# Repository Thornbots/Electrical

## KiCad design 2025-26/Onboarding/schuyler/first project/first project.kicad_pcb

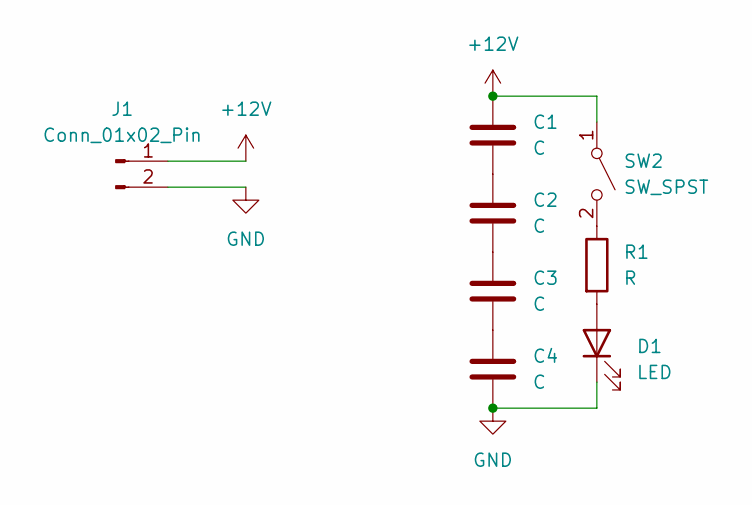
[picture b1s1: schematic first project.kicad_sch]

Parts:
C1, C2, C3, C4: C; CP_Radial_D18.0mm_P7.50mm
D1: LED; LED_D10.0mm
J1: Conn_01x02_Pin; AMASS_XT30PW-F_1x02_P2.50mm_Horizontal
R1: R; R_Axial_DIN0204_L3.6mm_D1.6mm_P5.08mm_Vertical
SW2: SW_SPST; SW_SPST_CK_RS282G05A3

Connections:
+12V: C1.1, J1.1, SW2.1 (A)
GND: C4.2, D1.1 (K), J1.2
unnamed: C1.2, C2.1
unnamed: C2.2, C3.1
unnamed: C3.2, C4.1
unnamed: D1.2 (A), R1.2
unnamed: R1.1, SW2.2 (B)

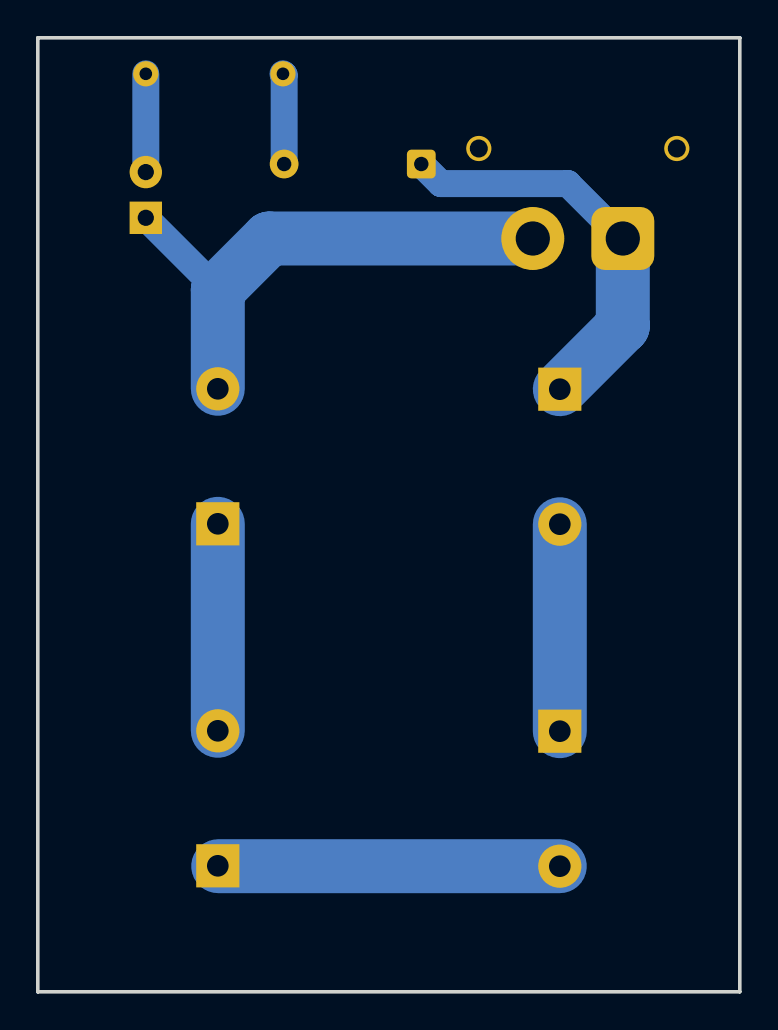
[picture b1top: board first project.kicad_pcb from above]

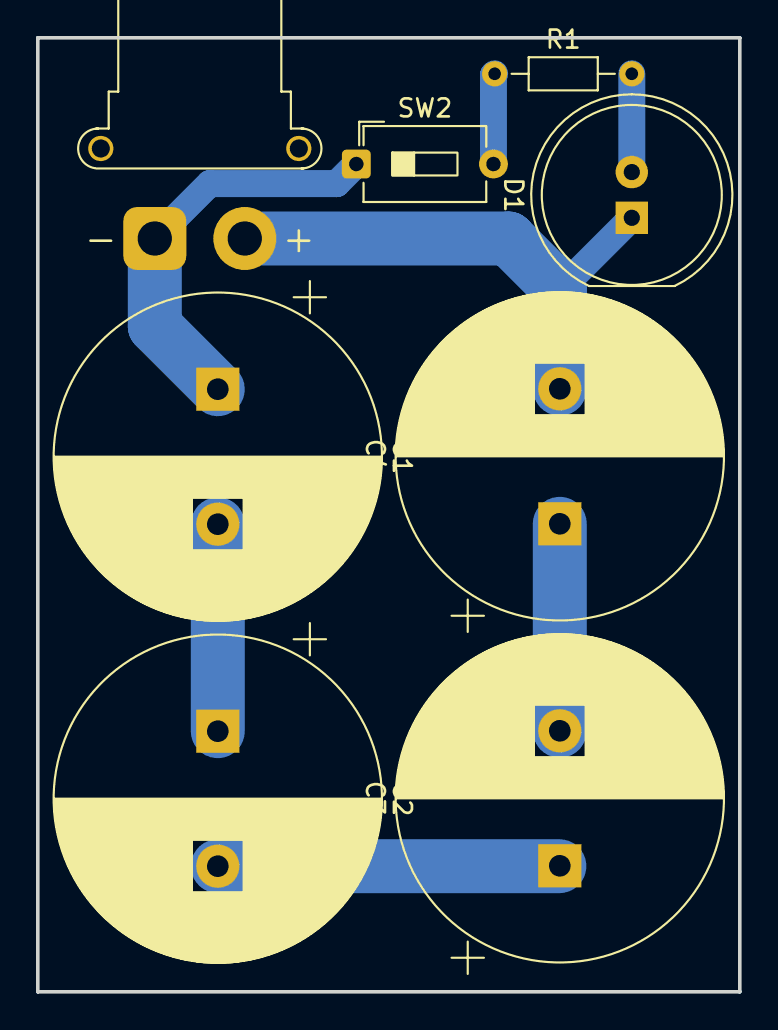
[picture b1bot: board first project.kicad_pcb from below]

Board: 2 copper layers, 39.0 x 53.0 mm, 8 parts (8 on the bottom side), 7 nets.

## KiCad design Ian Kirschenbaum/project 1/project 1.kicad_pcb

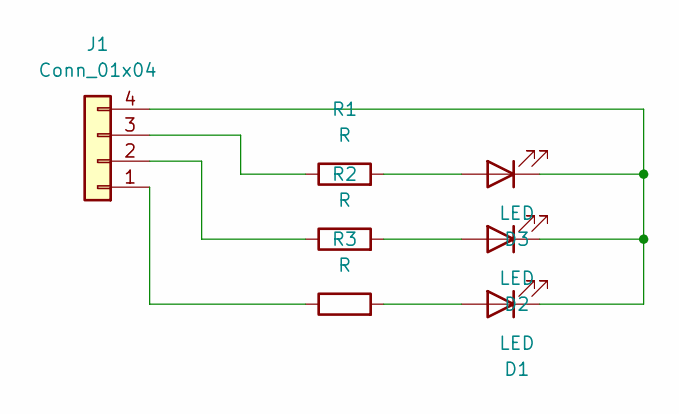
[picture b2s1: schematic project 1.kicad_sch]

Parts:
D1, D2, D3: LED
J1: Conn_01x04
R1, R2, R3: R

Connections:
unnamed: D1.2 (A), R3.2
unnamed: D1.1 (K), D2.1 (K), D3.1 (K), J1.4
unnamed: D2.2 (A), R2.2
unnamed: D3.2 (A), R1.2
unnamed: J1.1, R3.1
unnamed: J1.2, R2.1
unnamed: J1.3, R1.1

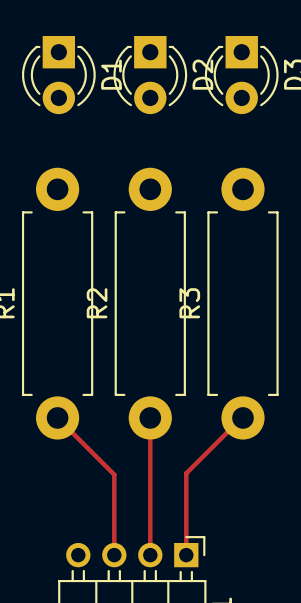
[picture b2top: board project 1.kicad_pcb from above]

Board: 2 copper layers, 7 parts (0 on the bottom side), 7 nets.

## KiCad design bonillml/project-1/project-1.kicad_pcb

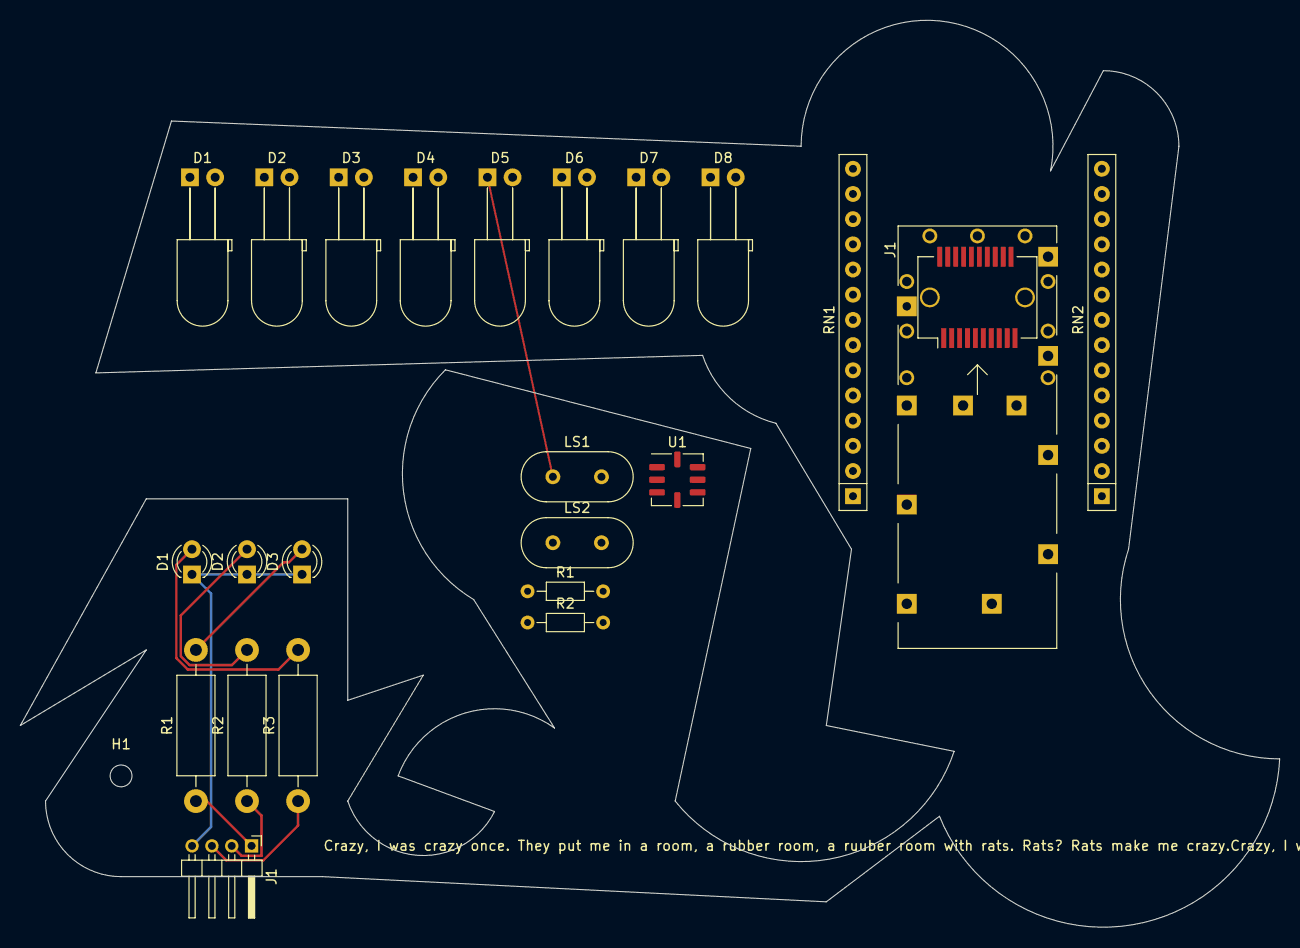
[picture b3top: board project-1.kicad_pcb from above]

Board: 2 copper layers, 127.0 x 91.5 mm, 24 parts (0 on the bottom side), 23 nets.

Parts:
D1, D2, D3, D4, D5, D6, D7, D8: LED; LED_D5.0mm_Horizontal_O6.35mm_Z9.0mm
D1#2, D2#2, D3#2: LED; LED_D3.0mm
H1: MountingHole; MountingHole_2.2mm_M2
J1: Conn_01x10_Pin; Connector_SFP_and_Cage
J1#2: Conn_01x04; PinHeader_1x04_P2.00mm_Horizontal
LS1, LS2: Speaker_Crystal; Crystal_HC18-U_Vertical
R1, R2#2: R; R_Axial_DIN0204_L3.6mm_D1.6mm_P7.62mm_Horizontal
R1#2, R2, R3: R; R_Axial_DIN0411_L9.9mm_D3.6mm_P15.24mm_Horizontal
RN1: R_Pack05; R_Array_SIP14
RN2: R_Pack02; R_Array_SIP14
U1: GM-402B; Winson_GM-402B_5x5mm_P1.27mm

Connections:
unnamed: D1.2 (A), D1#2.2 (A), R3.2, RN1.10 (R1.2)
unnamed: D1.1 (K), D1#2.1 (K), D2#2.1 (K), D3.2 (A), D3#2.1 (K), D7.1 (K), J1#2.4
unnamed: D2.2 (A), D2#2.2 (A), R2.2, RN1.9 (R2.2)
unnamed: D2.1 (K), D4.2 (A), D8.1 (K)
unnamed: D3#2.2 (A), R1#2.2
unnamed: D3.1 (K), D4.1 (K), D5.1 (K), J1.10, LS1.1, LS2.2, U1.1 (Rh1), U1.5 (Rs1)
unnamed: D5.2 (A), D6.1 (K)
unnamed: D6.2 (A), RN1.8 (R3.2)
unnamed: D7.2 (A), RN1.7 (R4.2)
unnamed: D8.2 (A), RN1.6 (R5.2)
unnamed: J1.1, J1#2.1, R1#2.1, RN1.1 (R1.1)
unnamed: J1.2, J1#2.2, R2.1, RN1.2 (R2.1)
unnamed: J1.3, J1#2.3, R3.1, RN1.3 (R3.1)
unnamed: J1.4, RN1.4 (R4.1)
unnamed: J1.5, RN1.5 (R5.1)
unnamed: J1.6, RN2.3 (R2.2)
unnamed: J1.7, RN2.4 (R1.2)
unnamed: J1.8, R1.1
unnamed: J1.9, R2#2.1
unnamed: LS1.2, R2#2.2
unnamed: LS2.1, R1.2
unnamed: RN2.1 (R1.1), U1.3 (Rh2)
unnamed: RN2.2 (R2.1), U1.7 (Rs2)

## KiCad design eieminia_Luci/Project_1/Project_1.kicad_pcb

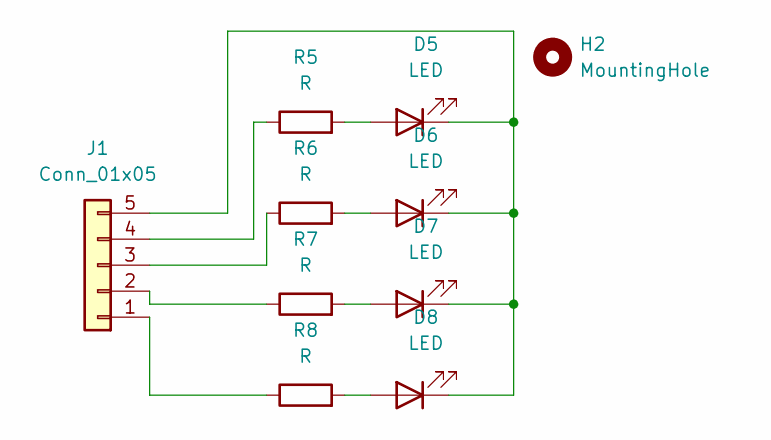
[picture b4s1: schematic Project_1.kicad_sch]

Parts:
D5, D6, D7, D8: LED; LED_D3.0mm
H2: MountingHole; MountingHole_2.1mm
J1: Conn_01x05; PinHeader_1x05_P2.54mm_Horizontal
R5, R6, R7, R8: R; R_Axial_DIN0309_L9.0mm_D3.2mm_P12.70mm_Horizontal

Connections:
unnamed: D5.2 (A), R5.2
unnamed: D5.1 (K), D6.1 (K), D7.1 (K), D8.1 (K), J1.5
unnamed: D6.2 (A), R6.2
unnamed: D7.2 (A), R7.2
unnamed: D8.2 (A), R8.2
unnamed: J1.1, R8.1
unnamed: J1.2, R7.1
unnamed: J1.3, R6.1
unnamed: J1.4, R5.1

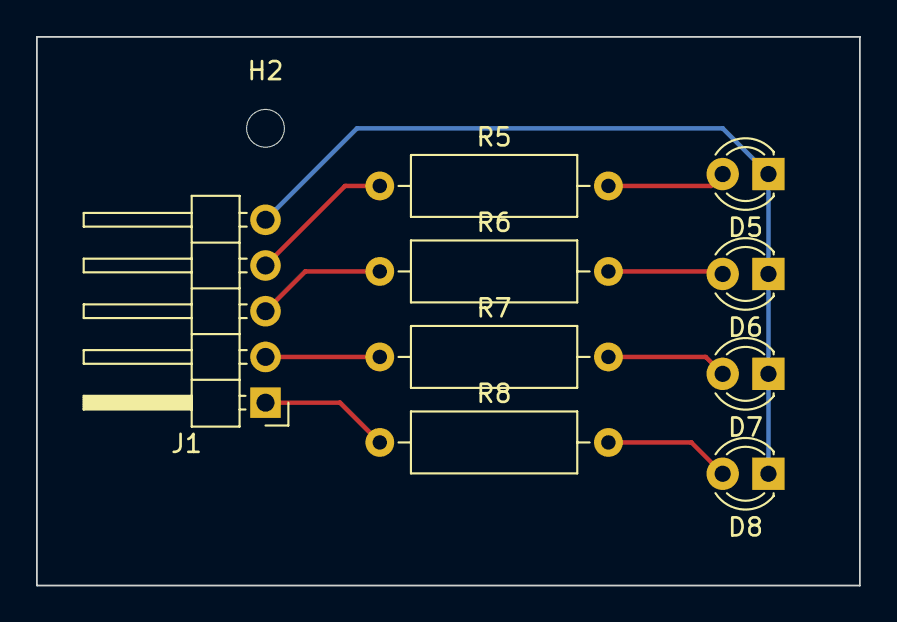
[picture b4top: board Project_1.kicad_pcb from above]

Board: 2 copper layers, 45.7 x 30.5 mm, 10 parts (0 on the bottom side), 9 nets.
